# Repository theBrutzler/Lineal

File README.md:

# Lineal
42cm

I created a board, that had known issues need 100k Ohm offset resistor

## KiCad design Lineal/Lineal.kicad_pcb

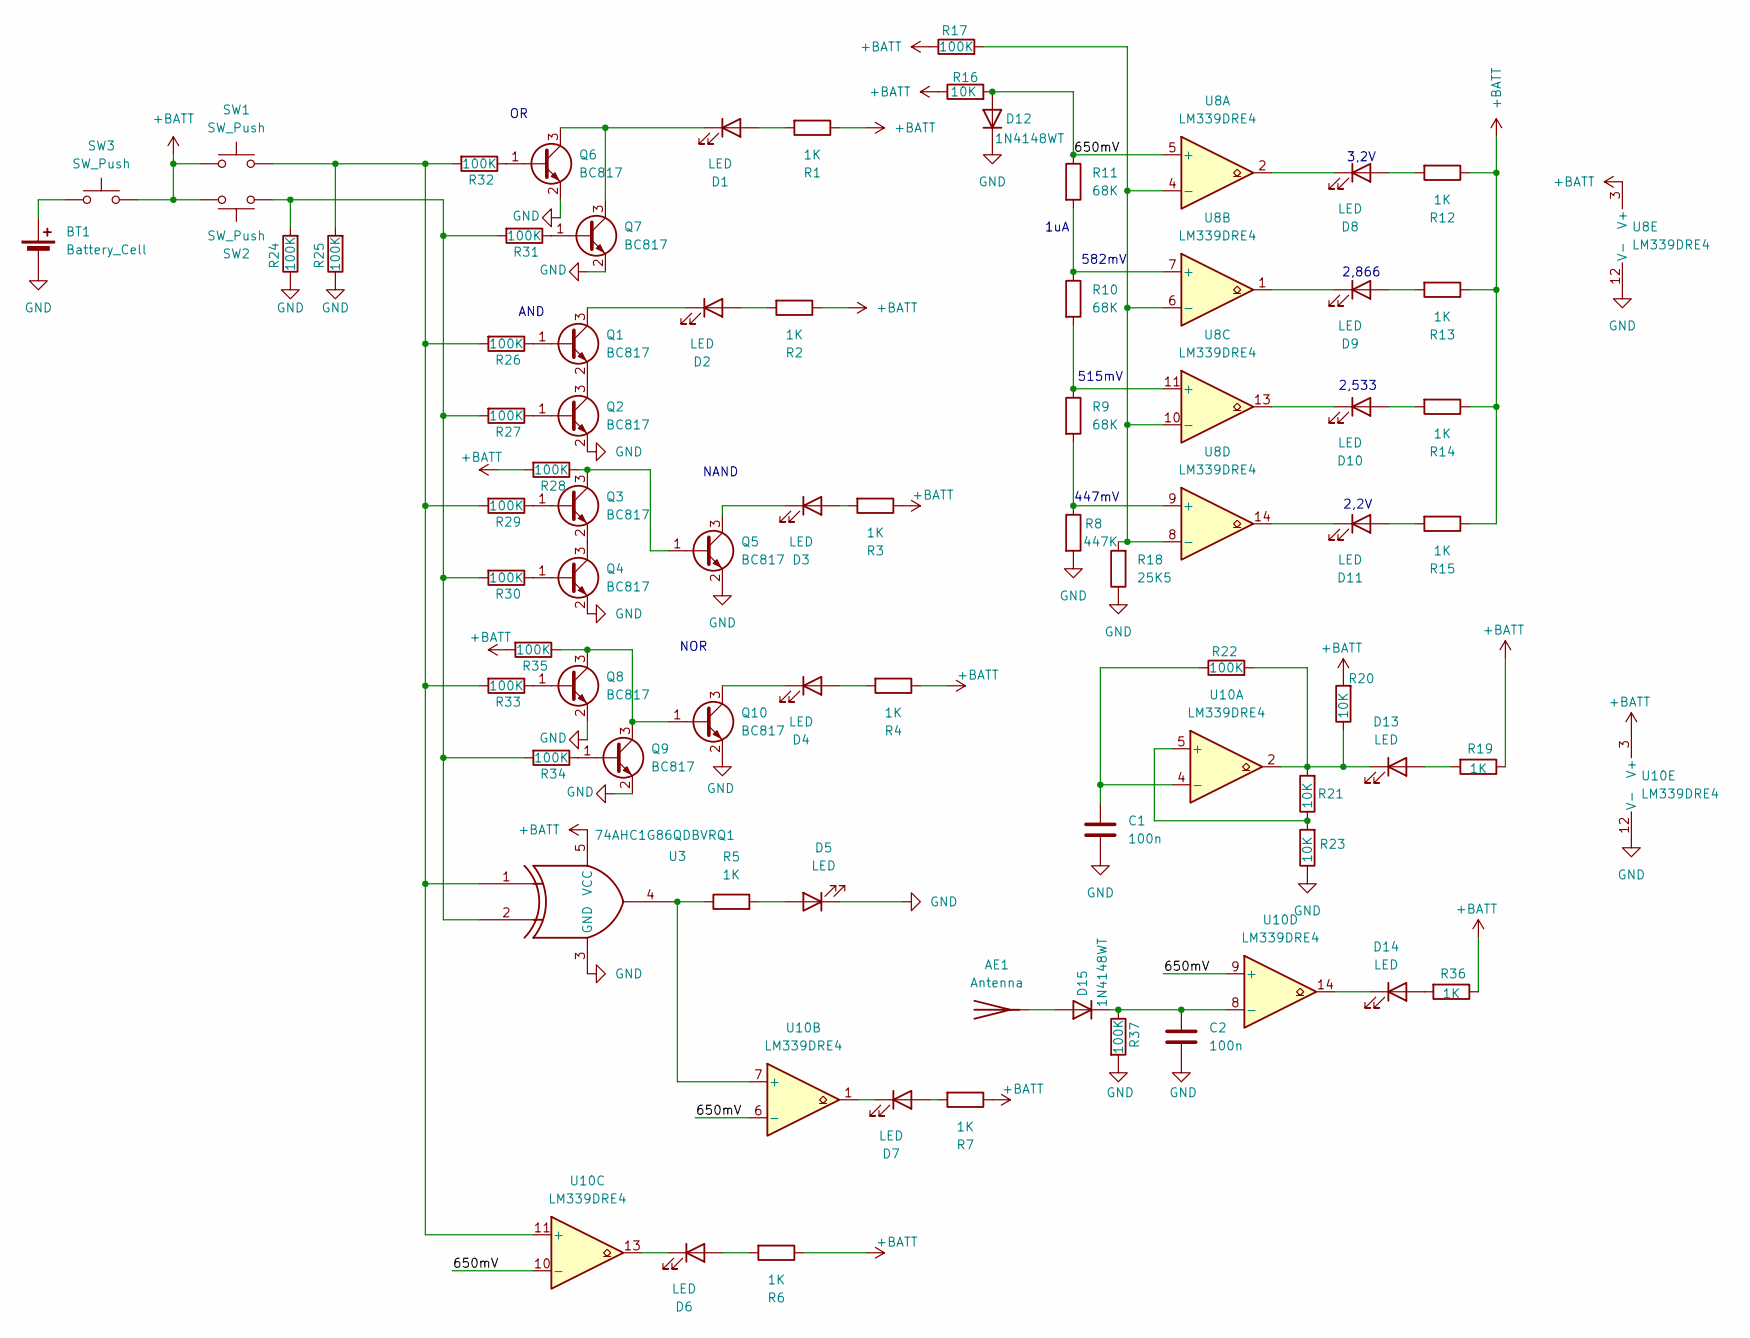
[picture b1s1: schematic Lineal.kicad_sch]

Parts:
AE1: Antenna
BT1: Battery_Cell; BatteryHolder_LINX_BAT-HLD-012-SMT
C1, C2: 100n; C_1206_3216Metric
D1, D2, D3, D4, D5, D6, D7, D8, D9, D10, D11, D13, D14: LED; LED_0603_1608Metric
D12, D15: 1N4148WT; D_SOD-523
Q1, Q2, Q3, Q4, Q5, Q6, Q7, Q8, Q9, Q10: BC817; SOT-23
R1, R2, R3, R4, R5, R6, R7, R12, R13, R14, R15, R19, R36: 1K; R_0603_1608Metric
R8: 447K; R_1206_3216Metric
R9, R10, R11: 68K; R_0603_1608Metric
R16, R20, R21, R23: 10K; R_0603_1608Metric
R17, R22, R24, R25, R26, R27, R28, R29, R30, R31, R32, R33, R34, R35, R37: 100K; R_0603_1608Metric
R18: 25K5; R_0402_1005Metric
SW1, SW2, SW3: SW_Push; SW_Push_1P1T_XKB_TS-1187A
U3: 74AHC1G86QDBVRQ1; SOT-23-5
U8, U10: LM339DRE4; SOIC-14_3.9x8.7mm_P1.27mm

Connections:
+BATT: R1.1, R2.1, R3.1, R4.1, R6.1, R7.1, R12.1, R13.1, R14.1, R15.1, R16.1, R17.1, R19.1, R20.2, R28.2, R35.2, R36.1, SW1.1, SW2.2, SW3.2, U3.5 (VCC), U8.3 (V+), U10.3 (V+)
/650mV: D12.2 (A), R11.1, R16.2, U8.5 (+), U10.6 (-), U10.9 (+), U10.10 (-)
GND: BT1.2 (-), C1.2, C2.2, D5.1 (K), D12.1 (K), Q2.2 (E), Q4.2 (E), Q5.2 (E), Q6.2 (E), Q7.2 (E), Q8.2 (E), Q9.2 (E), Q10.2 (E), R8.2, R18.1, R23.1, R24.1, R25.1, R37.2, U3.3 (GND), U8.12 (V-), U10.12 (V-)
unnamed: AE1.1, D15.2 (A)
unnamed: BT1.1 (+), SW3.1
unnamed: D1.2 (A), R1.2
unnamed: D1.1 (K), Q6.3 (C), Q7.3 (C)
unnamed: D2.2 (A), R2.2
unnamed: D2.1 (K), Q1.3 (C)
unnamed: D3.2 (A), R3.2
unnamed: D3.1 (K), Q5.3 (C)
unnamed: D4.2 (A), R4.2
unnamed: D4.1 (K), Q10.3 (C)
unnamed: D5.2 (A), R5.2
unnamed: D6.2 (A), R6.2
unnamed: D6.1 (K), U10.13
unnamed: D7.2 (A), R7.2
unnamed: D7.1 (K), U10.1
unnamed: D8.2 (A), R12.2
unnamed: D8.1 (K), U8.2
unnamed: D9.2 (A), R13.2
unnamed: D9.1 (K), U8.1
unnamed: D10.2 (A), R14.2
unnamed: D10.1 (K), U8.13
unnamed: D11.2 (A), R15.2
unnamed: D11.1 (K), U8.14
unnamed: D13.2 (A), R19.2
unnamed: D13.1 (K), R20.1, R21.2, R22.2, U10.2
unnamed: D14.2 (A), R36.2
unnamed: D14.1 (K), U10.14
unnamed: C2.1, D15.1 (K), R37.1, U10.8 (-)
unnamed: Q1.1 (B), R26.1
unnamed: Q1.2 (E), Q2.3 (C)
unnamed: Q2.1 (B), R27.1
unnamed: Q3.1 (B), R29.1
unnamed: Q3.3 (C), Q5.1 (B), R28.1
unnamed: Q3.2 (E), Q4.3 (C)
unnamed: Q4.1 (B), R30.1
unnamed: Q6.1 (B), R32.1
unnamed: Q7.1 (B), R31.1
unnamed: Q8.1 (B), R33.1
unnamed: Q9.1 (B), R34.1
unnamed: Q8.3 (C), Q9.3 (C), Q10.1 (B), R35.1
unnamed: R24.2, R27.2, R30.2, R31.2, R34.2, SW2.1, U3.2
unnamed: R17.2, R18.2, U8.4 (-), U8.6 (-), U8.8 (-), U8.10 (-)
unnamed: R10.1, R11.2, U8.7 (+)
unnamed: R9.1, R10.2, U8.11 (+)
unnamed: R8.1, R9.2, U8.9 (+)
unnamed: R21.1, R23.2, U10.5 (+)
unnamed: C1.1, R22.1, U10.4 (-)
unnamed: R5.1, U3.4, U10.7 (+)
unnamed: R25.2, R26.2, R29.2, R32.2, R33.2, SW1.2, U3.1, U10.11 (+)

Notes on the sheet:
AND
1uA
515mV
447mV
2,866
3,2V
2,2V
NAND
NOR
582mV
2,533

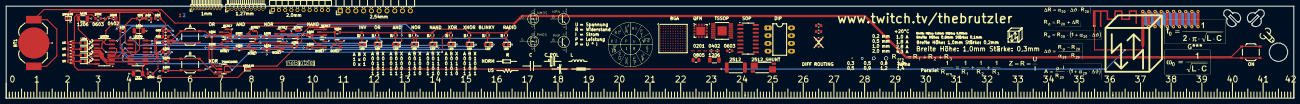
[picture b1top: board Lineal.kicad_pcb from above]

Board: 2 copper layers, 420.0 x 30.0 mm, 73 parts (0 on the bottom side), 51 nets.

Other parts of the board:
R37#2: 100K; R_0603_1608Metric
SM3: SYM_Arrow45_Tiny; Symbol_kurzschlussblog

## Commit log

2025-12-09 initial upload
2025-12-09 Update README with board description and image
    Added a description of the board and an image.
2025-12-09 Fix image link format in README.md
2025-12-09 Fix image link formatting in README.md
2025-12-09 Fix image link in README.md
2025-12-09 Update README with details on board issues
    Clarified the issue with the board by specifying the need for a 100k Ohm offset resistor.
2025-12-09 Add images to README for better visualization
2025-12-17 update html bom
2026-03-05 Update Possition an schematic pdf
